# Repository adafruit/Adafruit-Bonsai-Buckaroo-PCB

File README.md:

## Adafruit Bonsai Buckaroo PCB

<a href="http://www.adafruit.com/products/4534"><br/>
Click here to purchase one from the Adafruit shop</a>

PCB files for the Adafruit Bonsai Buckaroo. 

Format is EagleCAD schematic and board layout
* https://www.adafruit.com/product/4534

### Description

We can’t wait for spring to arrive, and we’re looking forward to caring for some plants! We designed this little add-on for micro:bit or CLUE boards – bolt it on with 5 screws to get a buzzer/beeper, motor driver, and breakouts for connecting a soil sensor (two alligator clips + nails work just fine). Simple, but effective!

* 8mm Buzzer/Speaker on pin P0 - have your plant kit beep when it wants watering, or have it sing a song when its nice and happy.
* 3V Motor control (on/off) on pin P2 - connect to a water pump to automatically water dry plants
* Alligator clip pads for pin P1, 3V and GND - connect to two alligator clips and nails to measure soil resistance

Works with micro:bit in Arduino, micropython or MakeCode. For CLUE, you can use CircuitPython or Arduino.

Please note this product does not come with a pump, tubing, alligator clips, nails, CLUE or micro:bit! It's just the control board that attaches to the micro:bit or CLUE!

### License

Adafruit invests time and resources providing this open source design, please support Adafruit and open-source hardware by purchasing products from [Adafruit](https://www.adafruit.com)!

Designed by Limor Fried/Ladyada for Adafruit Industries.

Creative Commons Attribution/Share-Alike, all text above must be included in any redistribution. 
See license.txt for additional details.

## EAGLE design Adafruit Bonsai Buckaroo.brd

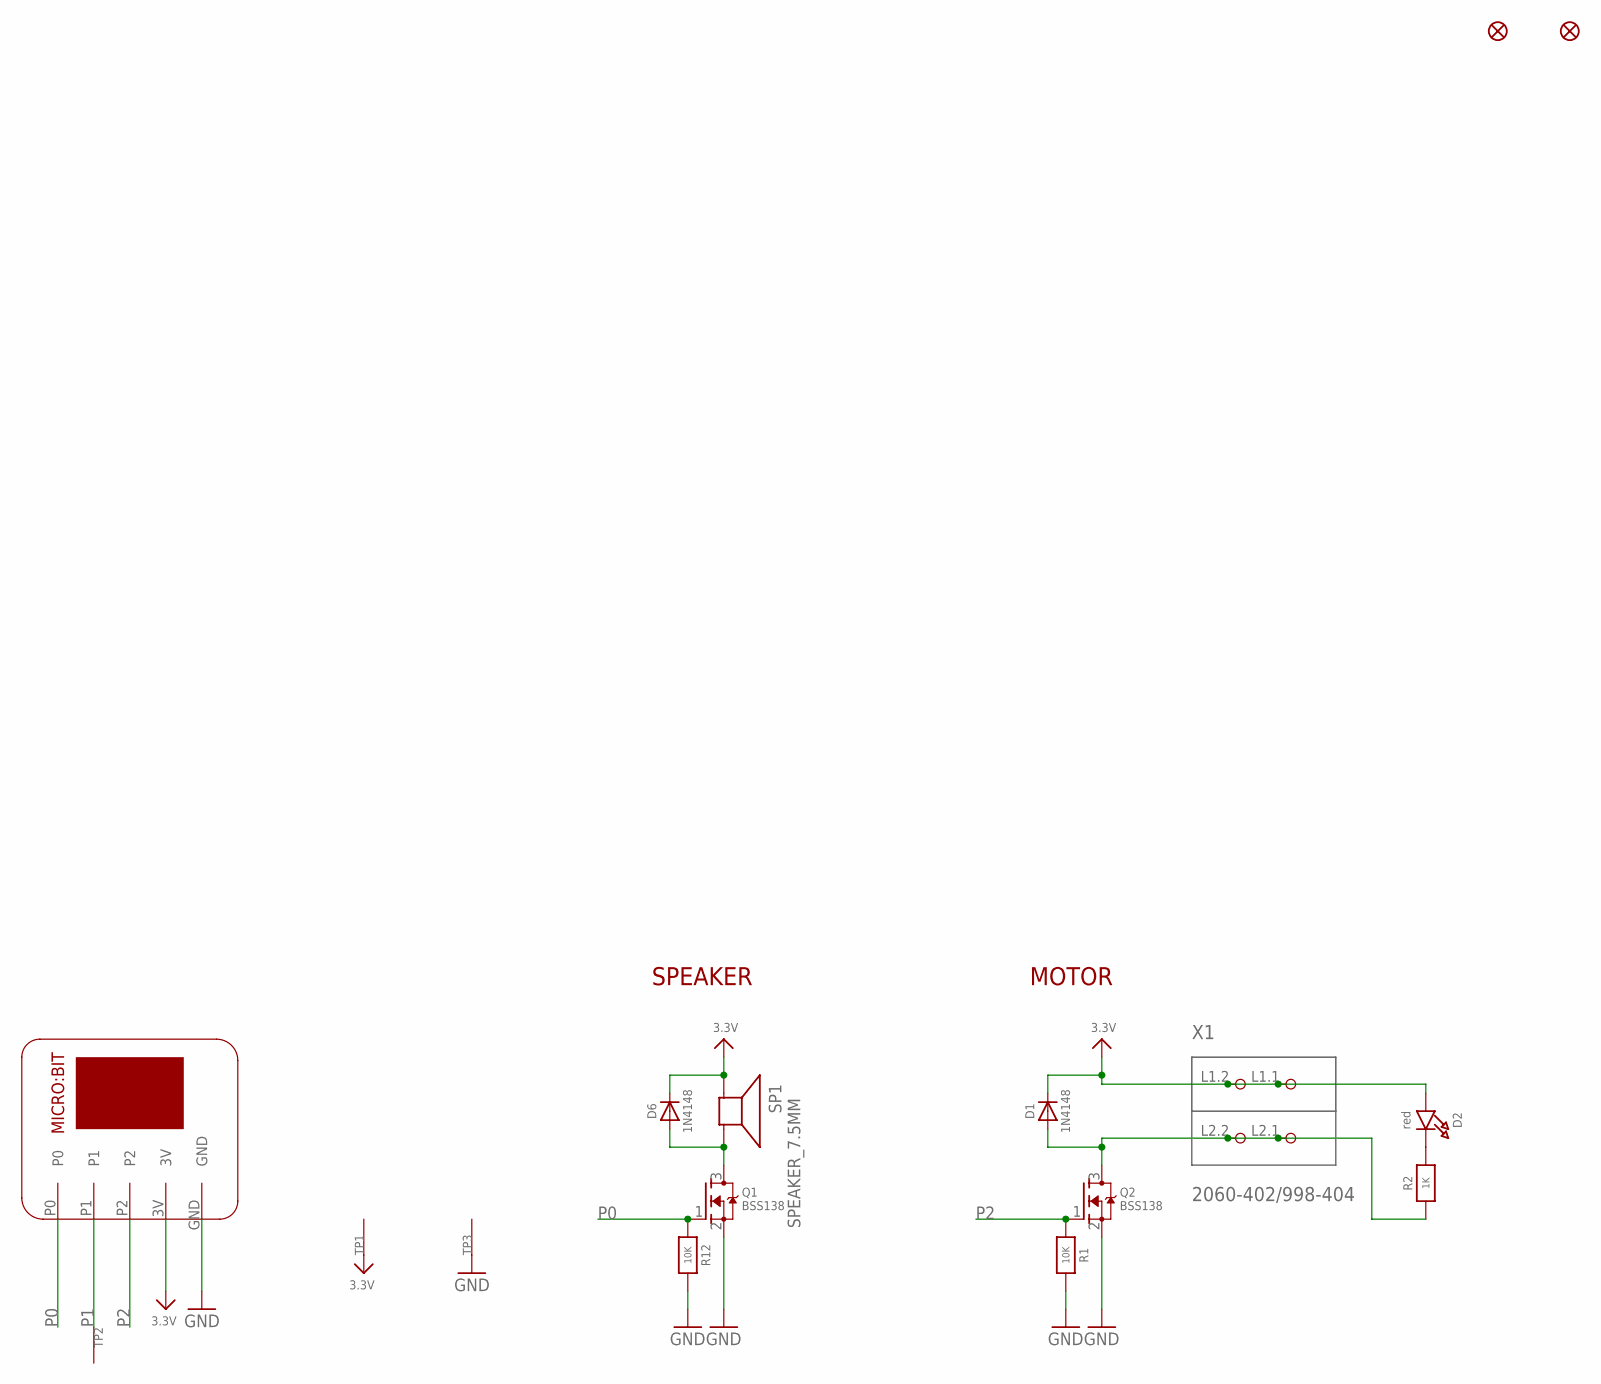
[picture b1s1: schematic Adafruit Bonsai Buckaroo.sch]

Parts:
D1, D6: 1N4148; SOD-323
D2: red; CHIPLED_0805_NOOUTLINE
FID1, FID2: FIDUCIAL_1MM
MB2: MICROBIT_5PIN; MICROBIT_5SMTNUT
Q1, Q2: BSS138; SOT23-WIDE
R1, R12: 10K; 0603-NO
R2: 1K; 0603-NO
SP1: SPEAKER_7.5MM; BUZZER_SMT_7.5MM
TP1, TP2, TP3: SEWTAPPCB_ALLIGATOR; PCB_ALLI
X1: 2060-402/998-404; P-2060-402/998-404

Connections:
3.3V: D1.C, D2.A, D6.C, MB2.3V, SP1.+, TP1.P$1, X1.L1.1 (P1.1), X1.L1.2 (P1.2)
GND: MB2.GND, Q1.2 (S), Q2.2 (S), R1.2, R12.2, TP3.P$1
unnamed: D1.A, Q2.3 (D), R2.1, X1.L2.1 (P2.1), X1.L2.2 (P2.2)
unnamed: D2.C, R2.2
unnamed: D6.A, Q1.3 (D), SP1.-
P0: MB2.P0, Q1.1 (G), R12.1
P1: MB2.P1, TP2.P$1
P2: MB2.P2, Q2.1 (G), R1.1

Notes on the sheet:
SPEAKER
MOTOR

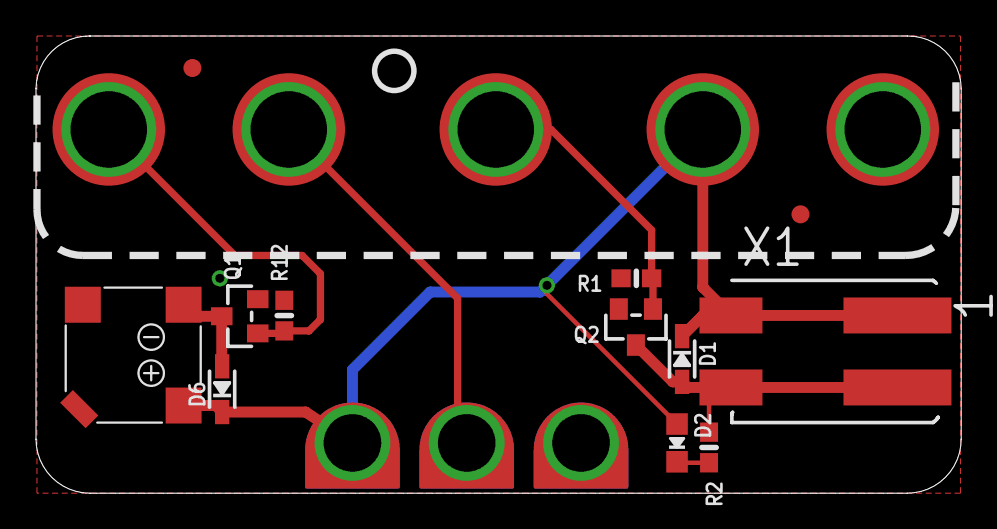
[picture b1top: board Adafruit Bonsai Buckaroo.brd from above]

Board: 2 copper layers, 51.4 x 25.4 mm, 19 parts (1 on the bottom side), 8 nets.

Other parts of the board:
U$4: BONSAI_BOT
U$5: BONSAI_TOP
U$10: PCBFEAT-REV-056

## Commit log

2020-03-19 Adding board files.

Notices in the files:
parts and their libraries:
microbuilder: This work is placed in the public domain, and may be freely used for commercial and non-commercial work with the following conditions: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
